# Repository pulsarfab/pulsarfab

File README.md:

# PulsarFab

Open-source astronomy hardware platform — dew heater controllers, power distribution and USB hubs, mount accessories, and other observatory gear based on STM32 and ESP32-S3 microcontrollers.

## Projects

| Project | Description | MCU | Flash/RAM | Framework | Status |
|---------|-------------|-----|-----------|-----------|--------|
| **pulsardew** | USB dew heater controller | STM32G0B1KBU6 | 128KB/144KB | STM32 HAL + FreeRTOS | 🚧 In Development |
| **[PulsarPower](hardware/pulsardewhub/README.md)** | Power distribution, two dew heaters and four-port USB 2.0 hub | STM32G0B1KBU6 | 128KB/144KB | Firmware adaptation pending | 🚧 Connected schematic / unrouted floorplan |
| **pulsardewpro** | WiFi dew heater controller (ASCOM Alpaca) | ESP32-S3-MINI-1 | 8MB/512KB | ESP-IDF | 🚧 In Development |
| **crunchdefender** | Skywatcher mount limit guard — inline USB host/device that interrupts motion before the OTA collides with the pier or cables crunch | STM32F405RGT6 | 1024KB/192KB | STM32 HAL | 🌱 Bootstrapped |

## Repository Structure

```
pulsarfab/
├── firmware/                 # All firmware projects (C/C++, Apache 2.0)
│   ├── pulsardew/             # STM32G0B1 USB dew heater controller
│   ├── pulsardewpro/          # ESP32-S3 WiFi dew heater (ASCOM Alpaca)
│   ├── crunchdefender/        # STM32F405 mount limit guard (dual-USB)
│   ├── common/                # Shared STM32 HAL and utilities
│   └── shared/                # Shared protocol definitions and libraries
├── hardware/                 # PCB designs (CERN-OHL-S v2 + NC)
│   ├── pulsardew/            # USB dew heater PCB
│   ├── pulsardewhub/         # PulsarPower power / dew / USB hub PCB
│   ├── pulsardewpro/         # WiFi dew heater PCB
│   ├── crunchdefender/       # Mount limit guard PCB
│   └── lib/                  # Shared KiCad libraries
├── mechanical/               # 3D models (coming soon, CERN-OHL-S v2 + NC)
└── LICENSE                   # Dual licensing information
```

## Quick Start

### Prerequisites

**For STM32 builds (pulsardew):**
- ARM GCC toolchain: `arm-none-eabi-gcc`
- CMake 3.20 or newer
- Make or Ninja build tool

**For ESP32-S3 builds (pulsardewpro):**
- ESP-IDF v5.x
- Python 3.10+
- uv (Python package manager)

See [firmware/README.md](firmware/README.md) for detailed installation instructions.

### Build Projects

```bash
# STM32 USB dew heater
cd firmware
make pulsardew-g0b1              # Build pulsardew (STM32G0B1)
make flash-pulsardew-g0b1        # Flash via st-flash

# STM32 mount limit guard
cd firmware
make crunchdefender-f405         # Build crunchdefender (STM32F405)
make flash-crunchdefender-f405   # Flash via st-flash

# ESP32-S3 WiFi dew heater
cd firmware/pulsardewpro
idf.py build                     # Build with ESP-IDF
idf.py flash                     # Flash via USB
```

## Key Features

### Dew Heater Control
- PWM-controlled heater outputs for telescope optics
- Temperature and humidity sensing (SHT40)
- Ambient dew point calculation with automatic heater regulation
- Configurable temperature setpoints per channel

### PulsarDew (USB)
- 4 PWM heater channels with current sensing
- Temperature/humidity sensor (SHT40 via I2C)
- USB 2.0 FS device (CDC for serial control from PC)
- Dew point calculation and automatic regulation
- Compact STM32G0B1 design with FreeRTOS

### PulsarDewPro (WiFi / ASCOM Alpaca)
- 4 PWM heater channels with individual current sensing
- Multiple temperature/humidity sensors
- WiFi 802.11 b/g/n connectivity
- ASCOM Alpaca REST API (ObservingConditions + Switch devices)
- Web configuration UI
- OTA firmware updates
- ESP32-S3 with ESP-IDF

### PulsarPower (Power / Dew / USB)
- Four independently switched, current-monitored DC outlets, **5 A service target each**
- Positive-side DC switching with grounded returns; static on/off, no PWM on DC outlets
- Two PWM dew heater channels
- Four external USB 2.0 ports, **500 mA per port**, plus an internal connection to the controller
- **12–18 V nominal input**, with alternative XT60 or barrel assembly options
- **25 A shared XT60 continuous target**; barrel option has a **3.5 A provisional continuous budget**
- **5 V / 3 A regulator** shared by USB and onboard electronics; not 3 A per USB port

PulsarDew remains the original dedicated dew controller. **PulsarPower** is the
expanded product, previously called **PulsarDew Hub** during development. Its
KiCad files and Makefile targets currently retain the `pulsardewhub` identifier.
The 0.3 draft has a connected schematic and an unrouted four-layer floorplan;
current ratings require routing and prototype qualification, and firmware
adaptation is pending. Cost reductions retain outlet current monitoring: TPS25974L
switches, one shared voltage window and two owned SiR680LDP input FETs. See the [PulsarPower design README](hardware/pulsardewhub/README.md)
for the power budget, schematic, floorplan and remaining release work.

PulsarPower and PulsarDew now share stocked XKB barrel sockets and HRO USB-C sockets;
SHT40 R2 is retained. The shared procurement CSV allocates 110 owned XKB sockets.
U30 now uses 22 allocated owned LMR51610s for the 20-board batch plus spares.
See the [LMR51610 implementation notes](hardware/pulsardewhub/docs/lmr51610-commonality.md)
for the 3.3 V / 650 mA logic stage; the 5 V / 3 A USB supply remains.

## Hardware

### PulsarDew (STM32G0B1KBU6)
- 128KB Flash, 144KB RAM
- ARM Cortex-M0+ @ 64MHz
- UFQFPN-32 package
- USB 2.0 FS (HSI48 + CRS, no external crystal)
- FreeRTOS real-time control

### PulsarDewPro (ESP32-S3-MINI-1)
- 8MB Flash, 512KB SRAM
- Dual-core Xtensa LX7 @ 240MHz
- WiFi 802.11 b/g/n
- USB-OTG for programming
- ASCOM Alpaca server

### CrunchDefender (STM32F405RGT6)
- 1024KB Flash, 192KB RAM (128KB SRAM + 64KB CCM)
- ARM Cortex-M4F @ 168MHz with single-precision FPU
- LQFP-64 package
- **Two USB peripherals running concurrently** — OTG_FS as device (PA11/PA12) to the host PC, OTG_HS-in-FS-mode as host (PB14/PB15) to the Skywatcher hand controller
- Sits inline on the USB link, parses position telemetry, intercepts motion commands when limits are exceeded

## License

This project uses dual licensing:

- **Firmware/Software**: [Apache 2.0](firmware/LICENSE)
- **Hardware Designs**: CERN-OHL-S v2 (strongly reciprocal) + Non-Commercial restriction

See [LICENSE](LICENSE) for details.

## Contributing

Contributions are welcome! Please ensure:
- Firmware contributions follow the Apache 2.0 license
- Hardware contributions follow CERN-OHL-S v2 + NC
- Code follows the existing style
- All changes are tested

## Resources

### Hardware
- [STM32G0 Series](https://www.st.com/en/microcontrollers-microprocessors/stm32g0-series.html)
- [ESP-IDF Documentation](https://docs.espressif.com/projects/esp-idf/)
- [ASCOM Alpaca](https://ascom-standards.org/Developer/Alpaca.htm)

### Licenses
- [Apache 2.0 License](https://www.apache.org/licenses/LICENSE-2.0)
- [CERN-OHL-S v2](https://ohwr.org/cern_ohl_s_v2.txt)

### Tools
- [uv Python Package Manager](https://github.com/astral-sh/uv)

---

Copyright (c) 2025-2026 Yann Ramin

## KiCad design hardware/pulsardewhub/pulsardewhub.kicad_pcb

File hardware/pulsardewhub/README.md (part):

# PulsarPower — power distribution, dew control and USB hub

**PulsarPower** is the expanded power product derived from the original
**[PulsarDew](../pulsardew/README.md)** dew heater controller. It combines four
switched DC outlets, two dew heaters and a four-port USB 2.0 hub. Earlier design
documents call it **PulsarDew Hub**; the directory, KiCad filenames and Makefile
targets currently retain `pulsardewhub` as their internal project identifier.

Revision **0.3-draft**, reviewed with KiCad 10.0.6 on 2026-10-03. Open
`pulsardewhub.kicad_pro` in KiCad. This is a separate design derived from
PulsarDew, with **two PWM heaters, four individually switched and current-monitored
DC outlets, and four external USB 2.0 ports**. DC outlets use static on/off GPIO;
they must not be PWM controlled.

The schematic is electrically connected and the native PCB is a placed,
**unrouted 180 × 110 mm four-layer floorplan**. It is not ready for fabrication.
There are no tracks, vias or copper fills. No enclosure is assumed.

Review the [15-page schematic PDF](docs/schematic.pdf) and
[annotated footprint placement](docs/pcb-placement.png) without opening KiCad.

## Ratings and assembly options

| Item | Design target / constraint |
| --- | --- |
| Input | **12–18 V DC (18 V maximum including supply tolerance)**, as selected for this revision |
| XT60 configuration | Fit J10 + F10; **25 A shared continuous target**, pending thermal/copper validation |
| Barrel configuration | Fit J11 + F11 instead; **5 A absolute total ceiling**, **3.5 A provisional continuous budget** after fuse derating |
| DC outlets | Four center-positive **2.0 mm** barrel sockets, 5 A service target each; independent high-side switch, analog current monitor and power-good signal |
| Heater outputs | Two screw terminals, 5 A target each; fused positive pin 1 and PWM switched return pin 2 |
| USB | Four USB-A downstream ports, 500 mA service per port; USB-C upstream data connection |

The **5 V regulator is rated for 3 A total**. Four USB ports reserve 2 A at
500 mA each; a provisional 0.6 A equivalent budget for onboard logic/support
leaves about 0.4 A margin. This is a design budget pending thermal and transient
testing, not an additional external 5 V output rating.

**Populate one input path only. Do not fit/connect both inputs.** J11 and F11
are DNP in the default XT60 assembly. There is no isolation between the two
input connector paths. The barrel option cannot support four loaded 5 A outlets.
At 20 A of DC outlet load, the XT60 target leaves about 5 A of input current for
the heaters, USB conversion and logic together. Six simultaneous 5 A loads are
outside this design budget. The external supply must be current limited and
the wiring/fuses must be coordinated with the final assembly.

F10 is a 30 A S1032 fuse; F11 is a 5 A Littelfuse 451. Heater fuses are 7 A
Littelfuse 451 devices to allow a 5 A service target after room-temperature
derating. Fuse markings are not continuous board-current ratings; ambient
temperature, enclosure, cable ratings and time/current curves still govern.

## Connected hierarchy

There are 15 schematic pages in nine source files. Root-sheet wires connect
the system rails, I2C, heater control, four DC interfaces and USB data/control.
Repeated sheets have distinct references and net identities.

| Sheet | Circuit |
| --- | --- |
| Power input | Alternative fused inputs, LM74700 + two parallel SiR680LDP reverse-polarity/reverse-current stage, SMCJ18A TVS, 470 µF bulk |
| DC supplies | LMR33630 input-to-5.02 V / 3 A; owned LMR51610 5 V-to-3.3 V logic stage, 650 mA budget |
| Controller | STM32G0B1KBU6, SWD/reset, SHT40, I2C pull-ups, ADC filters and GPIO connections |
| Heaters | TC4427A active-high gate driver, two AOD4184A switches, individual fuses/clamps, combined-current INA226 and 2 mΩ shunt |
| DC protection | One TPS3700 UV/OV window plus SN74LVC08 quad AND gate; four independent default-off commands |
| DC outlet ×4 | TPS25974LRPWR circuit breaker, local OVLO, ILM/current filter, latch-off, PG divider/pull-up, TVS1800 input clamp and SS54 output clamp |
| USB hub | USB2517, 24 MHz crystal, reset supervisor, configuration straps, protected USB-C upstream connection |
| USB port ×4 | TPS2553 current-limited VBUS switch, USBLC6 ESD, USB-A socket, 150 µF bulk and ceramic bypass |

The seven-port USB2517 uses port 1 for the onboard STM32 and ports 2–5 for the
four external sockets. Ports 6 and 7 are disabled by straps. The hub is
self-powered, with individual downstream power control. Its two internal 1.8 V
regulator outputs each have their own capacitor and are not tied together.
Host VBUS is used only for detection and upstream ESD protection, with no
connection to the board's 5 V supply. The selected 150 µF ±20% downstream
capacitors retain at least 120 µF at nominal tolerance.

The LM74700 input circuit is not an overvoltage disconnect. Do not apply more
than 18 V nominal; the TVS is for transients, not sustained excess input voltage.
DC output switches have no external reverse-blocking FET, so **do not backfeed
the DC outlets**. Heater return pins must not be connected directly to ground.

## MCU interface and firmware changes

| Function | STM32 signal / physical pad |
| --- | --- |
| Heater 0 / 1 | PA0 / PA1, pads 7 / 8, active-high PWM |
| DC enable 1 / 2 / 3 / 4 | PB0 / PB1 / PB2 / PB9, pads 15 / 16 / 17 / 1; static GPIO only |
| DC current ADC 1–4 | PA4–PA7, pads 11–14 |
| DC power-good 1 / 2 / 3 / 4 | PB3 / PB4 / PB5 / PC6, pads 27 / 28 / 29 / 20; high = output ready |
| USB D− / D+ | PA11 / PA12, pads 22 / 23, internal hub port 1 |
| USB attach permission | PA9, pad 19, hub port 1 PWR output |
| I2C SCL / SDA | PB6 / PB7, pads 30 / 31; INA226 0x40, SHT40 0x44 |
| SWDIO / SWCLK / NRST | PA13 / PA14 / PF2, pads 24 / 25 / 6 |

The original firmware is not a drop-in image: heater polarity and channel count,
ADC inputs, outlet GPIO and hub attachment behavior have changed. Disable the
MCU UCPD dead-battery function on PA9, and detach USB whenever USB_ATTACH is low.
Initialize heater and DC enables low. Overcurrent/thermal faults latch off until
reset through the enable signal; do not repeatedly retry a short circuit.
`DC_PG1..4` replaces the former `DC_FLT1..4` labels on the same MCU pins. PG low
also means disabled, starting, or voltage-inhibited. Qualify PG against the
commanded state and allow startup settling. The voltage window is an automatic
hardware inhibit: recovery can re-enable a still-asserted GPIO and can reset a
latched fault by pulling EN low. Firmware should deassert ENABLE after an
unexpected PG loss if an explicit user restart is required.

Heater inputs and gates have pull-downs, and the new non-inverting driver
addresses the original driver's dependence on a live 3.3 V rail for default-off
behavior. Validate startup, brownout and loss of each rail on hardware; this is
not a certified safety shutdown. The INA226 measures **combined heater current**;
the four DC currents are measured independently through TPS25974 ILM outputs.

With a **1 kΩ ILM resistor**, the nominal ADC slope is **0.1055 V/A**
(**0.5275 V at 5 A**). ILM sets the breaker threshold and provides the current
signal. The 10 kΩ / 10 nF filter isolates ADC capacitance from this pin; do not
put a capacitor directly on ILM. Gain limits are 98–114 µA/A for currents from
1 A to the configured limit. Include source impedance in ADC acquisition-time
settings and calibrate each channel. Readings during a short are not guaranteed.

The nominal breaker setting is **5747 / 1000 = 5.747 A**, allowing a **5 A
service target**. A ±10% threshold screening plus 1% resistor tolerance and an
additional 1% TCR allowance gives approximately **5.07–6.45 A**; this calculation
is not a substitute for measured trip/no-trip limits. ITIMER is open for the
fastest response. The **L** variant latches after overcurrent/thermal faults;
cycle enable to recover. The separate fast-trip threshold is nominally 2.01×
ILIM (1.70–2.40× specified ratio). The 4.7 nF slew capacitor targets 0.702 V/ms,
or about 25.6 ms at 18 V. Verify startup with actual capacitive loads.

One **TPS3700** provides the common hardware voltage window: **9.2 V rising
UV** and **19.2 V rising OV**, using 220 kΩ/10 kΩ and 470 kΩ/10 kΩ dividers.
Its open-drain outputs are tied together and pulled up through 10 kΩ. A
**SN74LVC08** computes `outlet_enable[i] = command[i] AND window_ok` independently
for each port. Each command has a 10 kΩ pull-down. Each eFuse has a 10 kΩ enable
pull-down and 1 kΩ series input resistor. The shared window is a common failure
point, not a redundant safety circuit. Reset, brownout and loss-of-rail tests
remain required.

Each eFuse retains its own fast OVLO divider (150 kΩ / 10 kΩ, 19.2 V nominal;
about 18.57–20.04 V including thresholds, resistor tolerances and leakage).
PGTH uses 100 kΩ / 20 kΩ for about 7.2 V rising. PG high also requires completion
of startup; it is an output-ready indication, not a precision output voltmeter.
Neither inhibit disconnects VIN from the ICs, bucks or heaters. Recovery can
re-enable an asserted GPIO, so firmware must deassert the command after an
unexpected PG loss when manual restart is required.

The new eFuse supports −40°C to +125°C junction temperature; **−15°C remains the
accepted lower product target**. Its input absolute maximum is 28 V. Each old
SMBJ18A local clamp was replaced by **TVS1800DRVR**, whose 24.7 V maximum clamp
applies to the datasheet's specified 35 A, 8/20 µs, 125°C pulse condition. This
leaves voltage margin, but does not establish a system surge rating: final
loops, source impedance, pulse energy and overshoot must be tested. The TVS1800
has an 18 V standoff rating; supply tolerance must stay within that limit.

**Q10 and Q11 are parallel SiR680LDP input MOSFETs from shared stock.** They are
80 V parts with ±20 V gates and 2.5 V maximum threshold. At 25 A total, equal
sharing and 3.55 mΩ maximum RDS(on) at 4.5 V gate drive/25°C give **1.11 W total**
conduction loss. Applying an illustrative 1.6× hot-resistance factor gives
1.78 W total; current sharing and temperature remain layout/bench checks.
Use symmetric short source/drain paths, common low-inductance gate routing,
and thermal copper. The Vishay PowerPAK SO-8 footprint uses pad 5 for the
exposed drain and physical drain leads 5–8; source is 1–3 and gate is 4.
C10 is now 1 µF/50 V, exceeding LM74700's `10 × combined Ciss` recommendation
(145 nF for two 7.25 nF devices) with substantial capacitance margin. C13 adds
local raw-input bypass. Gate charge is 90 nC typical/135 nC maximum **per FET at
10 V**, and startup/body-diode stress must be checked with the selected supply.

## PCB floorplan and routing intent

The floorplan contains 226 schematic footprints, four M3 holes and three
fiducials. Mount centers are 4 mm from the edges (172 × 102 mm spacing).
USB connectors occupy the top edge; their switches, ESD devices and bulk caps
are nearby. The hub is behind the downstream ports with the MCU to its left.
DC switches and their output connectors occupy four regions along the bottom.
The two heater stages occupy the lower-left region. Input protection and bucks
sit at the left. SHT40 is at the right edge, with a copper keepout beneath the
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
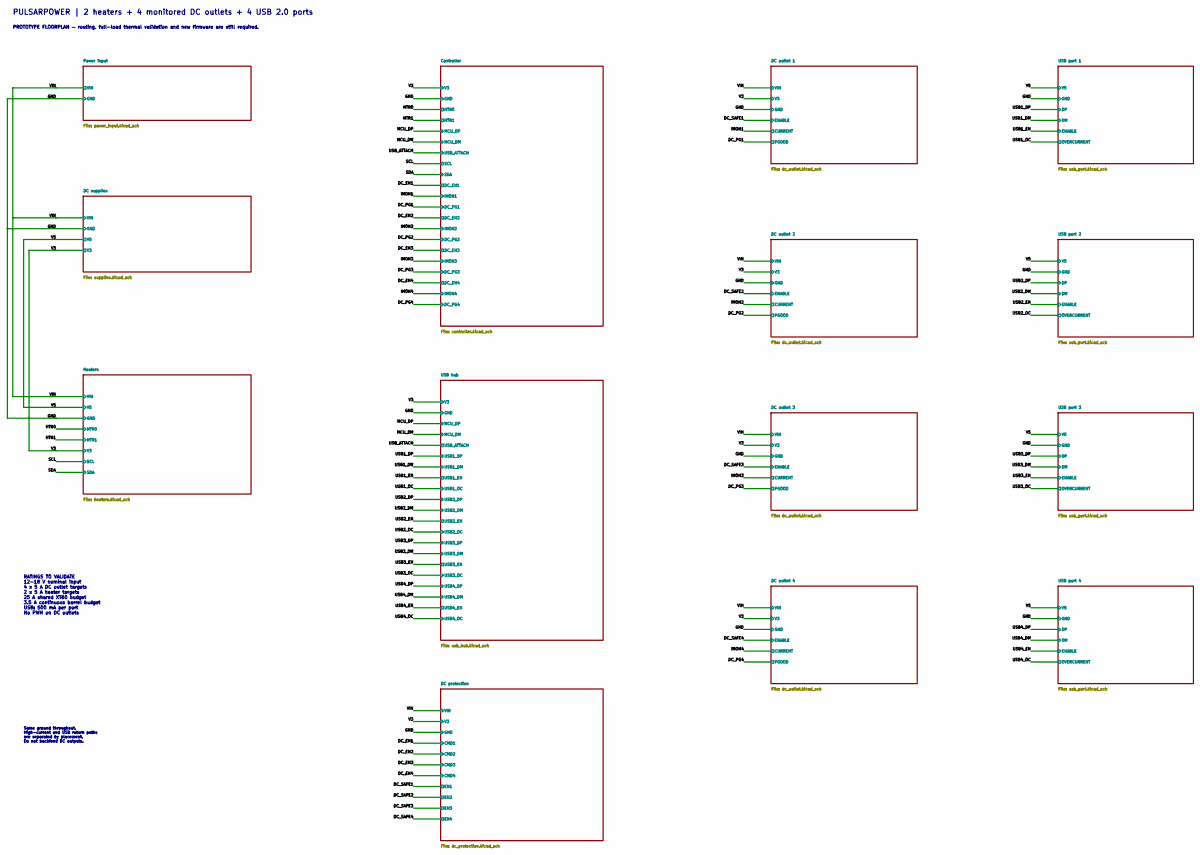
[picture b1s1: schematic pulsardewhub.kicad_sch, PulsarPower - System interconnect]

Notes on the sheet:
PULSARPOWER | 2 heaters + 4 monitored DC outlets + 4 USB 2.0 ports
PROTOTYPE FLOORPLAN — routing, full-load thermal validation and new firmware are still required.
RATINGS TO VALIDATE 12-18 V nominal input 4 x 5 A DC outlet targets 2 x 5 A heater targets 25 A shared XT60 budget 3.5 A continuous barrel budget USB: 500 mA per port No PWM on DC outlets
Same ground throughout. High-current and USB return paths are separated by placement. Do not backfeed DC outputs.

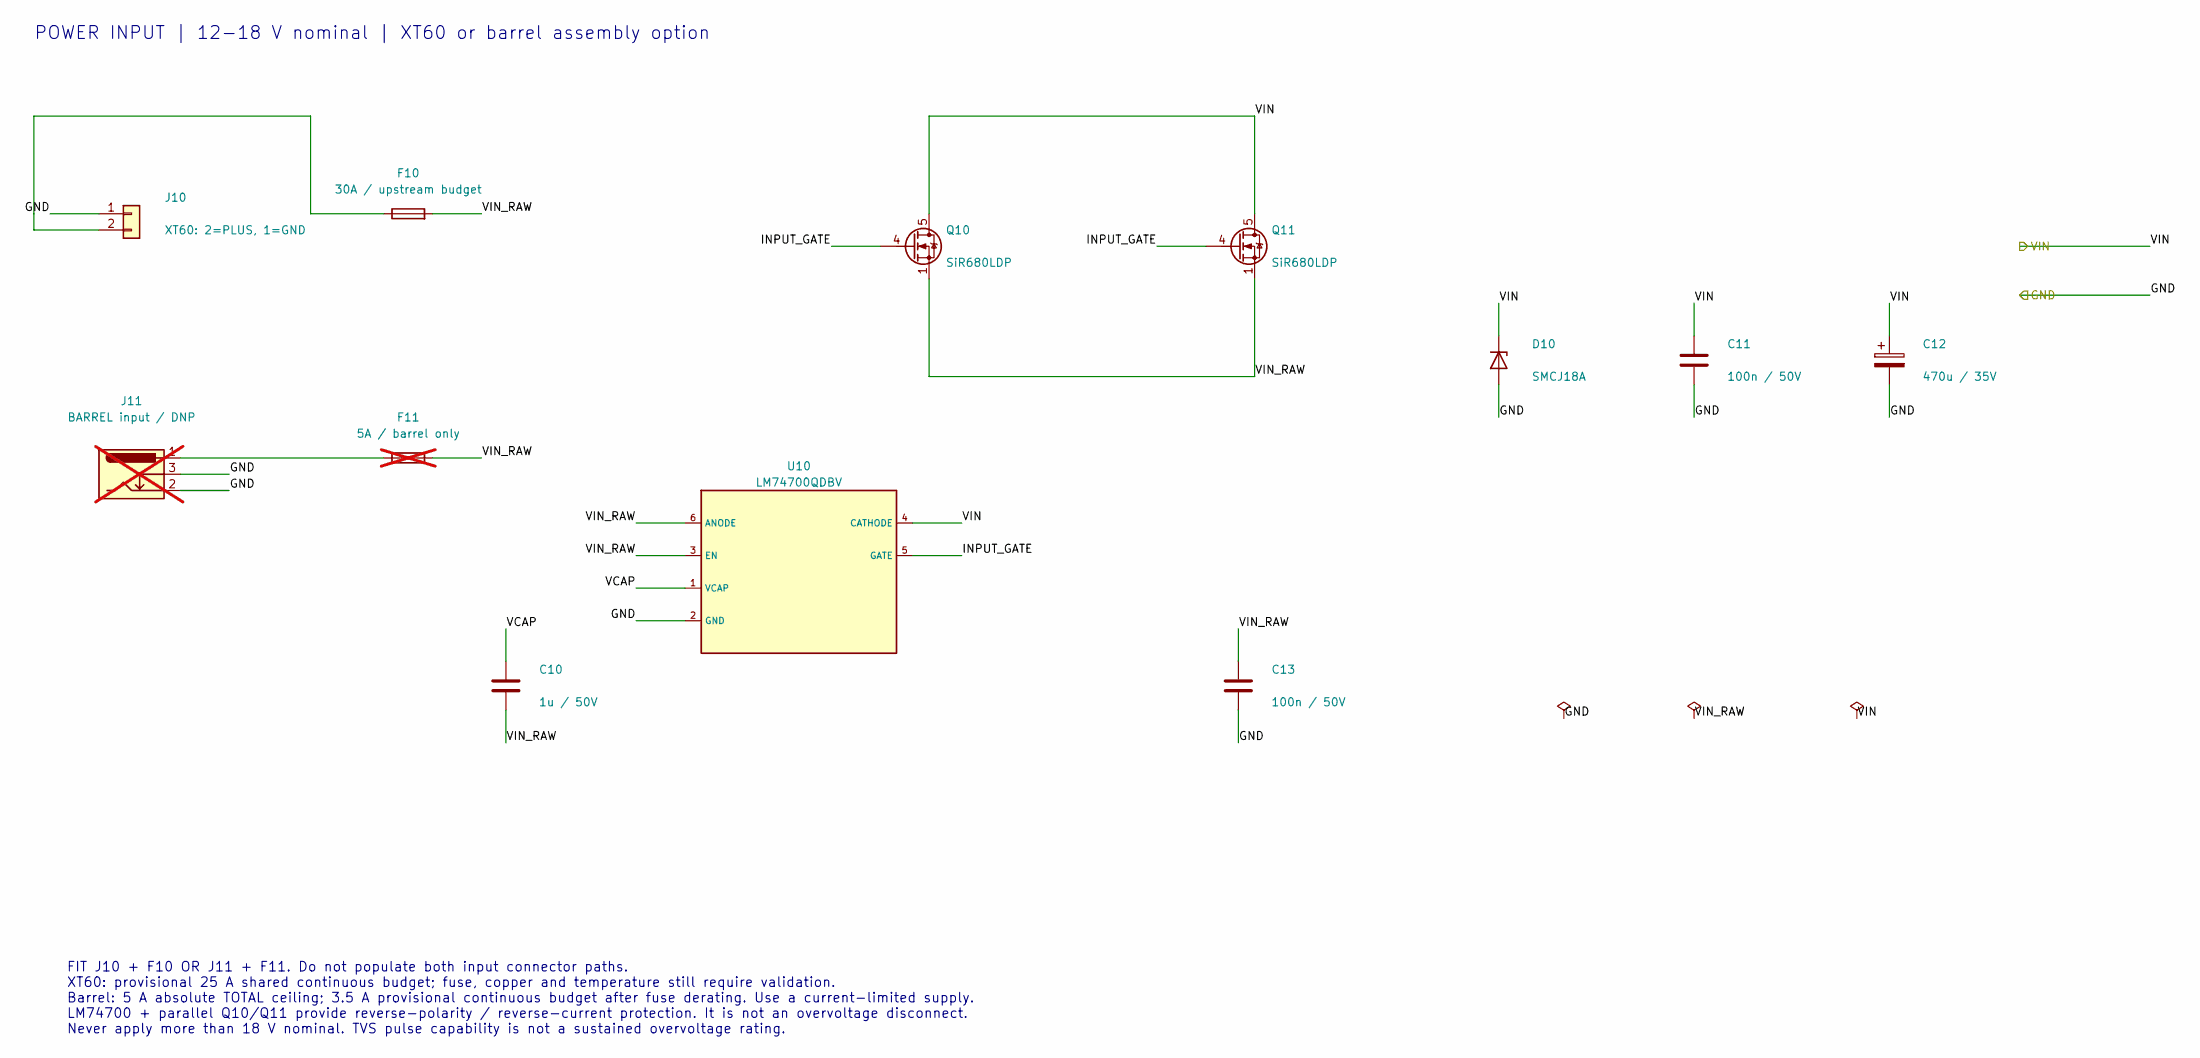
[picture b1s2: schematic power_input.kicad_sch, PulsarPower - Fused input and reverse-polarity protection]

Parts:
C10: 1u / 50V; C_0603_1608Metric; MPN CL10A105KB8NNNC; LCSC C15849
C11, C13: 100n / 50V; C_0603_1608Metric; MPN CC0603KRX7R9BB104; LCSC C14663
C12: 470u / 35V; CP_Radial_D10.0mm_P5.00mm; MPN ERS1VM471G16OT; LCSC C106703
D10: SMCJ18A; D_SMC; MPN SMCJ18A; LCSC C438102
F10: 30A / upstream budget; Fuse_S1032_10.3x3.2mm; MPN S1032-F-30.0A; LCSC C553917
F11: 5A / barrel only; Fuse_Littelfuse-NANO2-451_453; MPN 0451005.MRL; LCSC C48467; not fitted
J10: XT60: 2=PLUS, 1=GND; AMASS_XT60PW-M_Edge; MPN XT60PW-M; LCSC C98732
J11: BARREL input / DNP; BarrelJack_XKB_DC-005K-5A_Edge; MPN DC-005K-5A-2.0; LCSC C2880546; not fitted
Q10, Q11: SiR680LDP; PowerPAK_SO-8_Single; MPN SIR680LDP-T1-RE3; LCSC C3279524
U10: LM74700QDBV; SOT-23-6; MPN LM74700QDBVRQ1; LCSC C2941042

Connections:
/GND: C11.2, C12.2, C13.2, D10.2 (A), J10.1, J11.2, J11.3, U10.2 (GND); also elsewhere on the board
/Power input/INPUT_GATE: Q10.4 (G), Q11.4 (G), U10.5 (GATE)
/Power input/VCAP: C10.1, U10.1 (VCAP)
/Power input/VIN_RAW: C10.2, C13.1, F10.2, F11.2, Q10.1 (S), Q10.2 (S), Q10.3 (S), Q11.1 (S), Q11.2 (S), Q11.3 (S), U10.3 (EN), U10.6 (ANODE)
/VIN: C11.1, C12.1, D10.1 (K), Q10.5 (D), Q11.5 (D), U10.4 (CATHODE); also elsewhere on the board
unnamed: F11.1, J11.1
unnamed: F10.1, J10.2

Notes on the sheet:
POWER INPUT | 12-18 V nominal | XT60 or barrel assembly option
FIT J10 + F10 OR J11 + F11. Do not populate both input connector paths. XT60: provisional 25 A shared continuous budget; fuse, copper and temperature still require validation. Barrel: 5 A absolute TOTAL ceiling; 3.5 A provisional continuous budget after fuse derating. Use a current-limited supply. 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

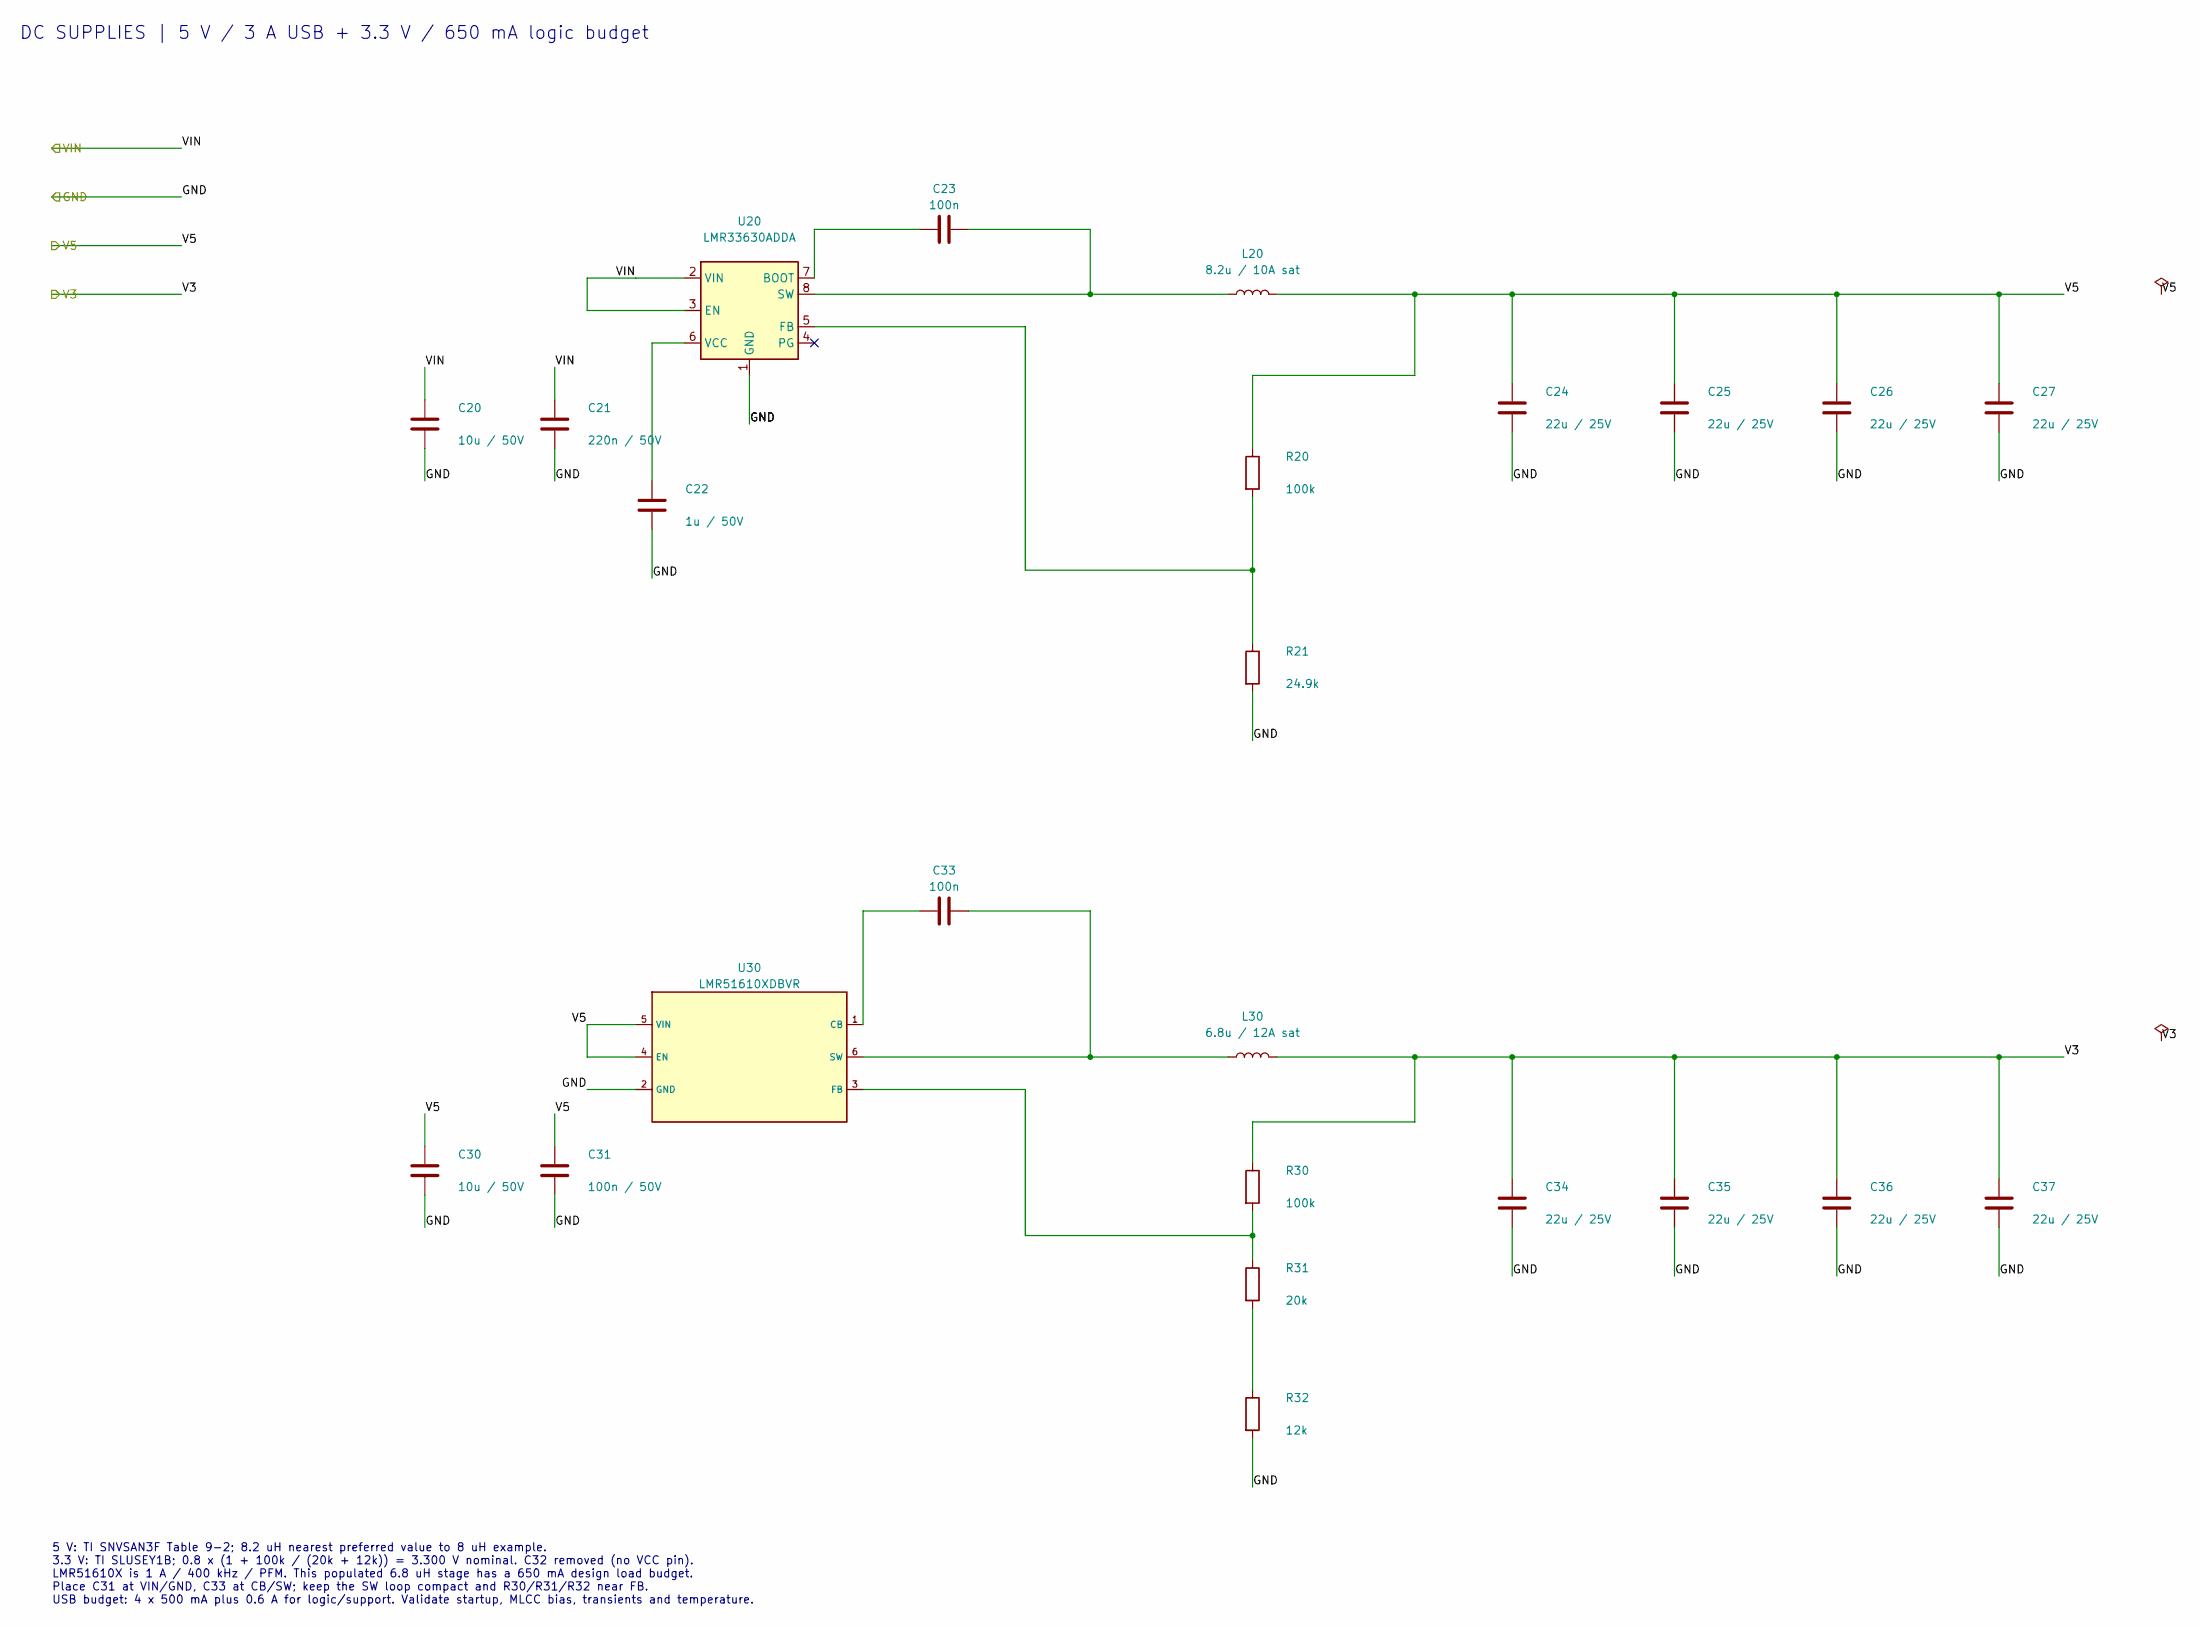
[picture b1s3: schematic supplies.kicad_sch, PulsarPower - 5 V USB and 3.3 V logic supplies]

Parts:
C20, C30: 10u / 50V; C_1210_3225Metric; MPN CL32B106KBJNNNE; LCSC C138687
C21: 220n / 50V; C_0603_1608Metric; MPN CL10B224KB8NNNC; LCSC C64705
C22: 1u / 50V; C_0603_1608Metric; MPN CL10A105KB8NNNC; LCSC C15849
C23, C33: 100n; C_0603_1608Metric; MPN CC0603KRX7R9BB104; LCSC C14663
C24, C25, C26, C27, C34, C35, C36, C37: 22u / 25V; C_1206_3216Metric; MPN CL31A226KAHNNNE; LCSC C12891
C31: 100n / 50V; C_0603_1608Metric; MPN CC0603KRX7R9BB104; LCSC C14663
L20: 8.2u / 10A sat; L_SXN_SMMS1050; MPN SMMS1050-8R2M; LCSC C149543
L30: 6.8u / 12A sat; L_SXN_SMMS1050; MPN SMMS1050-6R8M; LCSC C149542
R20, R30: 100k; R_0603_1608Metric; MPN 0603WAF1003T5E; LCSC C25803
R21: 24.9k; R_0603_1608Metric; MPN 0603WAF2492T5E; LCSC C25962
R31: 20k; R_0603_1608Metric; MPN 0603WAF2002T5E; LCSC C4184
R32: 12k; R_0603_1608Metric; MPN 0603WAF1202T5E; LCSC C22790
U20: LMR33630ADDA; Texas_HSOP-8-1EP_3.9x4.9mm_P1.27mm; MPN LMR33630ADDAR; LCSC C841384
U30: LMR51610XDBVR; SOT-23-6; MPN LMR51610XDBVR; LCSC C20539658

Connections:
/GND: C20.2, C21.2, C22.2, C24.2, C25.2, C26.2, C27.2, C30.2, C31.2, C34.2, C35.2, C36.2, C37.2, R21.2, R32.2, U20.1 (GND), U20.9 (GND), U30.2 (GND); also elsewhere on the board
/V3: C34.1, C35.1, C36.1, C37.1, L30.2, R30.1; also elsewhere on the board
/V5: C24.1, C25.1, C26.1, C27.1, C30.1, C31.1, L20.2, R20.1, U30.4 (EN), U30.5 (VIN); also elsewhere on the board
/VIN: C20.1, C21.1, U20.2 (VIN), U20.3 (EN); also elsewhere on the board
unnamed: R31.2, R32.1
unnamed: C23.1, U20.7 (BOOT)
unnamed: R20.2, R21.1, U20.5 (FB)
unnamed: C23.2, L20.1, U20.8 (SW)
unnamed: C22.1, U20.6 (VCC)
unnamed: C33.1, U30.1 (CB)
unnamed: R30.2, R31.1, U30.3 (FB)
unnamed: C33.2, L30.1, U30.6 (SW)

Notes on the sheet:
DC SUPPLIES | 5 V / 3 A USB + 3.3 V / 650 mA logic budget
5 V: TI SNVSAN3F Table 9-2; 8.2 uH nearest preferred value to 8 uH example. 3.3 V: TI SLUSEY1B; 0.8 x (1 + 100k / (20k + 12k)) = 3.300 V nominal. C32 removed (no VCC pin). LMR51610X is 1 A / 400 kHz / PFM. This populated 6.8 uH stage has a 650 mA design load budget. Place C31 at VIN/GND, C33 at CB/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

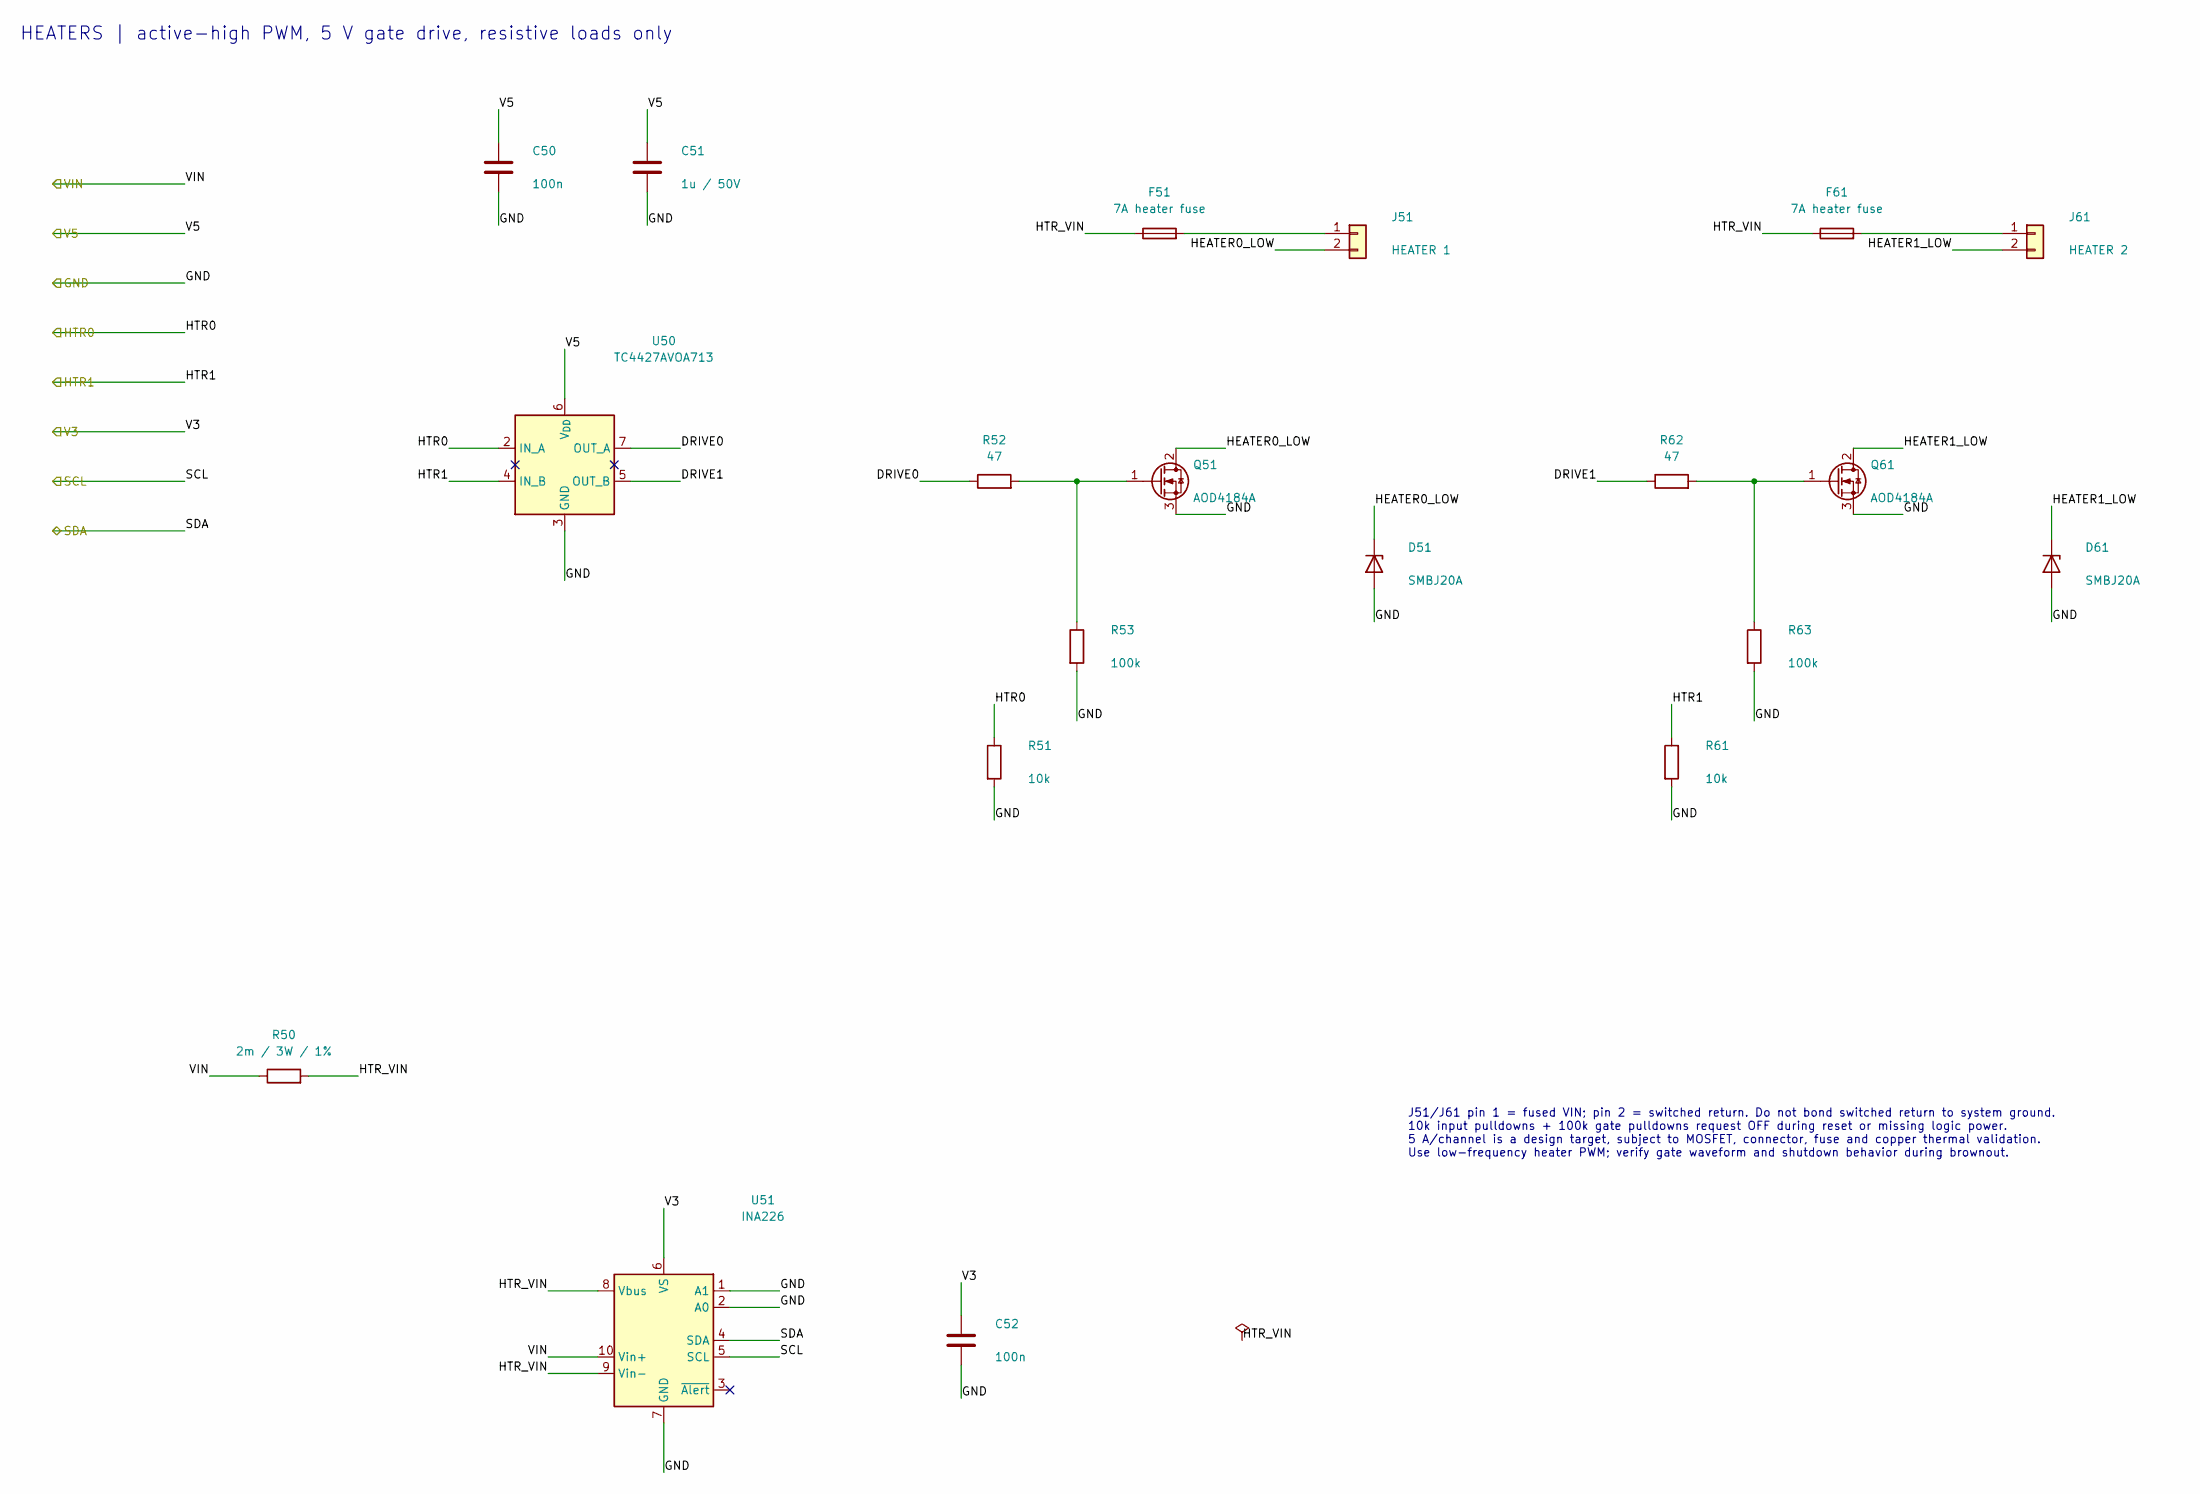
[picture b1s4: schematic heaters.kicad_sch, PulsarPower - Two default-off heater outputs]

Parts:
C50, C52: 100n; C_0603_1608Metric; MPN CC0603KRX7R9BB104; LCSC C14663
C51: 1u / 50V; C_0603_1608Metric; MPN CL10A105KB8NNNC; LCSC C15849
D51, D61: SMBJ20A; D_SMB; MPN SMBJ20A; LCSC C364296
F51, F61: 7A heater fuse; Fuse_Littelfuse-NANO2-451_453; MPN 0451007.MRL; LCSC C99548
J51: HEATER 1; TerminalBlock_KEFA_KF128_2P_P5.08mm; MPN KF128-5.08-2P-AA; LCSC C474952
J61: HEATER 2; TerminalBlock_KEFA_KF128_2P_P5.08mm; MPN KF128-5.08-2P-AA; LCSC C474952
Q51, Q61: AOD4184A; TO-252-2; MPN AOD4184A; LCSC C5370959
R50: 2m / 3W / 1%; R_2512_6332Metric; MPN HoLLR2512-3W-2mR-1%; LCSC C2994640
R51, R61: 10k; R_0603_1608Metric; MPN 0603WAF1002T5E; LCSC C25804
R52, R62: 47; R_0603_1608Metric; MPN 0603WAF470JT5E; LCSC C23182
R53, R63: 100k; R_0603_1608Metric; MPN 0603WAF1003T5E; LCSC C25803
U50: TC4427AVOA713; SOIC-8_3.9x4.9mm_P1.27mm; MPN TC4427AVOA713; LCSC C624944
U51: INA226; TSSOP-10_3x3mm_P0.5mm; MPN INA226AIDGSR; LCSC C49851

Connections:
/GND: C50.2, C51.2, C52.2, D51.2 (A), D61.2 (A), Q51.3 (S), Q61.3 (S), R51.2, R53.2, R61.2, R63.2, U50.3 (GND), U51.1 (A1), U51.2 (A0), U51.7 (GND); also elsewhere on the board
/HTR0: R51.1, U50.2 (IN_A); also elsewhere on the board
/HTR1: R61.1, U50.4 (IN_B); also elsewhere on the board
/Heaters/DRIVE0: R52.1, U50.7 (OUT_A)
/Heaters/DRIVE1: R62.1, U50.5 (OUT_B)
/Heaters/HEATER0_LOW: D51.1 (K), J51.2, Q51.2 (D)
/Heaters/HEATER1_LOW: D61.1 (K), J61.2, Q61.2 (D)
/Heaters/HTR_VIN: F51.1, F61.1, R50.2, U51.8 (Vbus), U51.9 (Vin-)
/SCL: U51.5 (SCL); also elsewhere on the board
/SDA: U51.4 (SDA); also elsewhere on the board
/V3: C52.1, U51.6 (VS); also elsewhere on the board
/V5: C50.1, C51.1, U50.6 (V_{DD}); also elsewhere on the board
/VIN: R50.1, U51.10 (Vin+); also elsewhere on the board
unnamed: F51.2, J51.1
unnamed: F61.2, J61.1
unnamed: Q51.1 (G), R52.2, R53.1
unnamed: Q61.1 (G), R62.2, R63.1

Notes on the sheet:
HEATERS | active-high PWM, 5 V gate drive, resistive loads only
J51/J61 pin 1 = fused VIN; pin 2 = switched return. Do not bond switched return to system ground. 10k input pulldowns + 100k gate pulldowns request OFF during reset or missing logic power. 5 A/channel is a design target, subject to MOSFET, connector, fuse and copper thermal validation. Use low-freq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

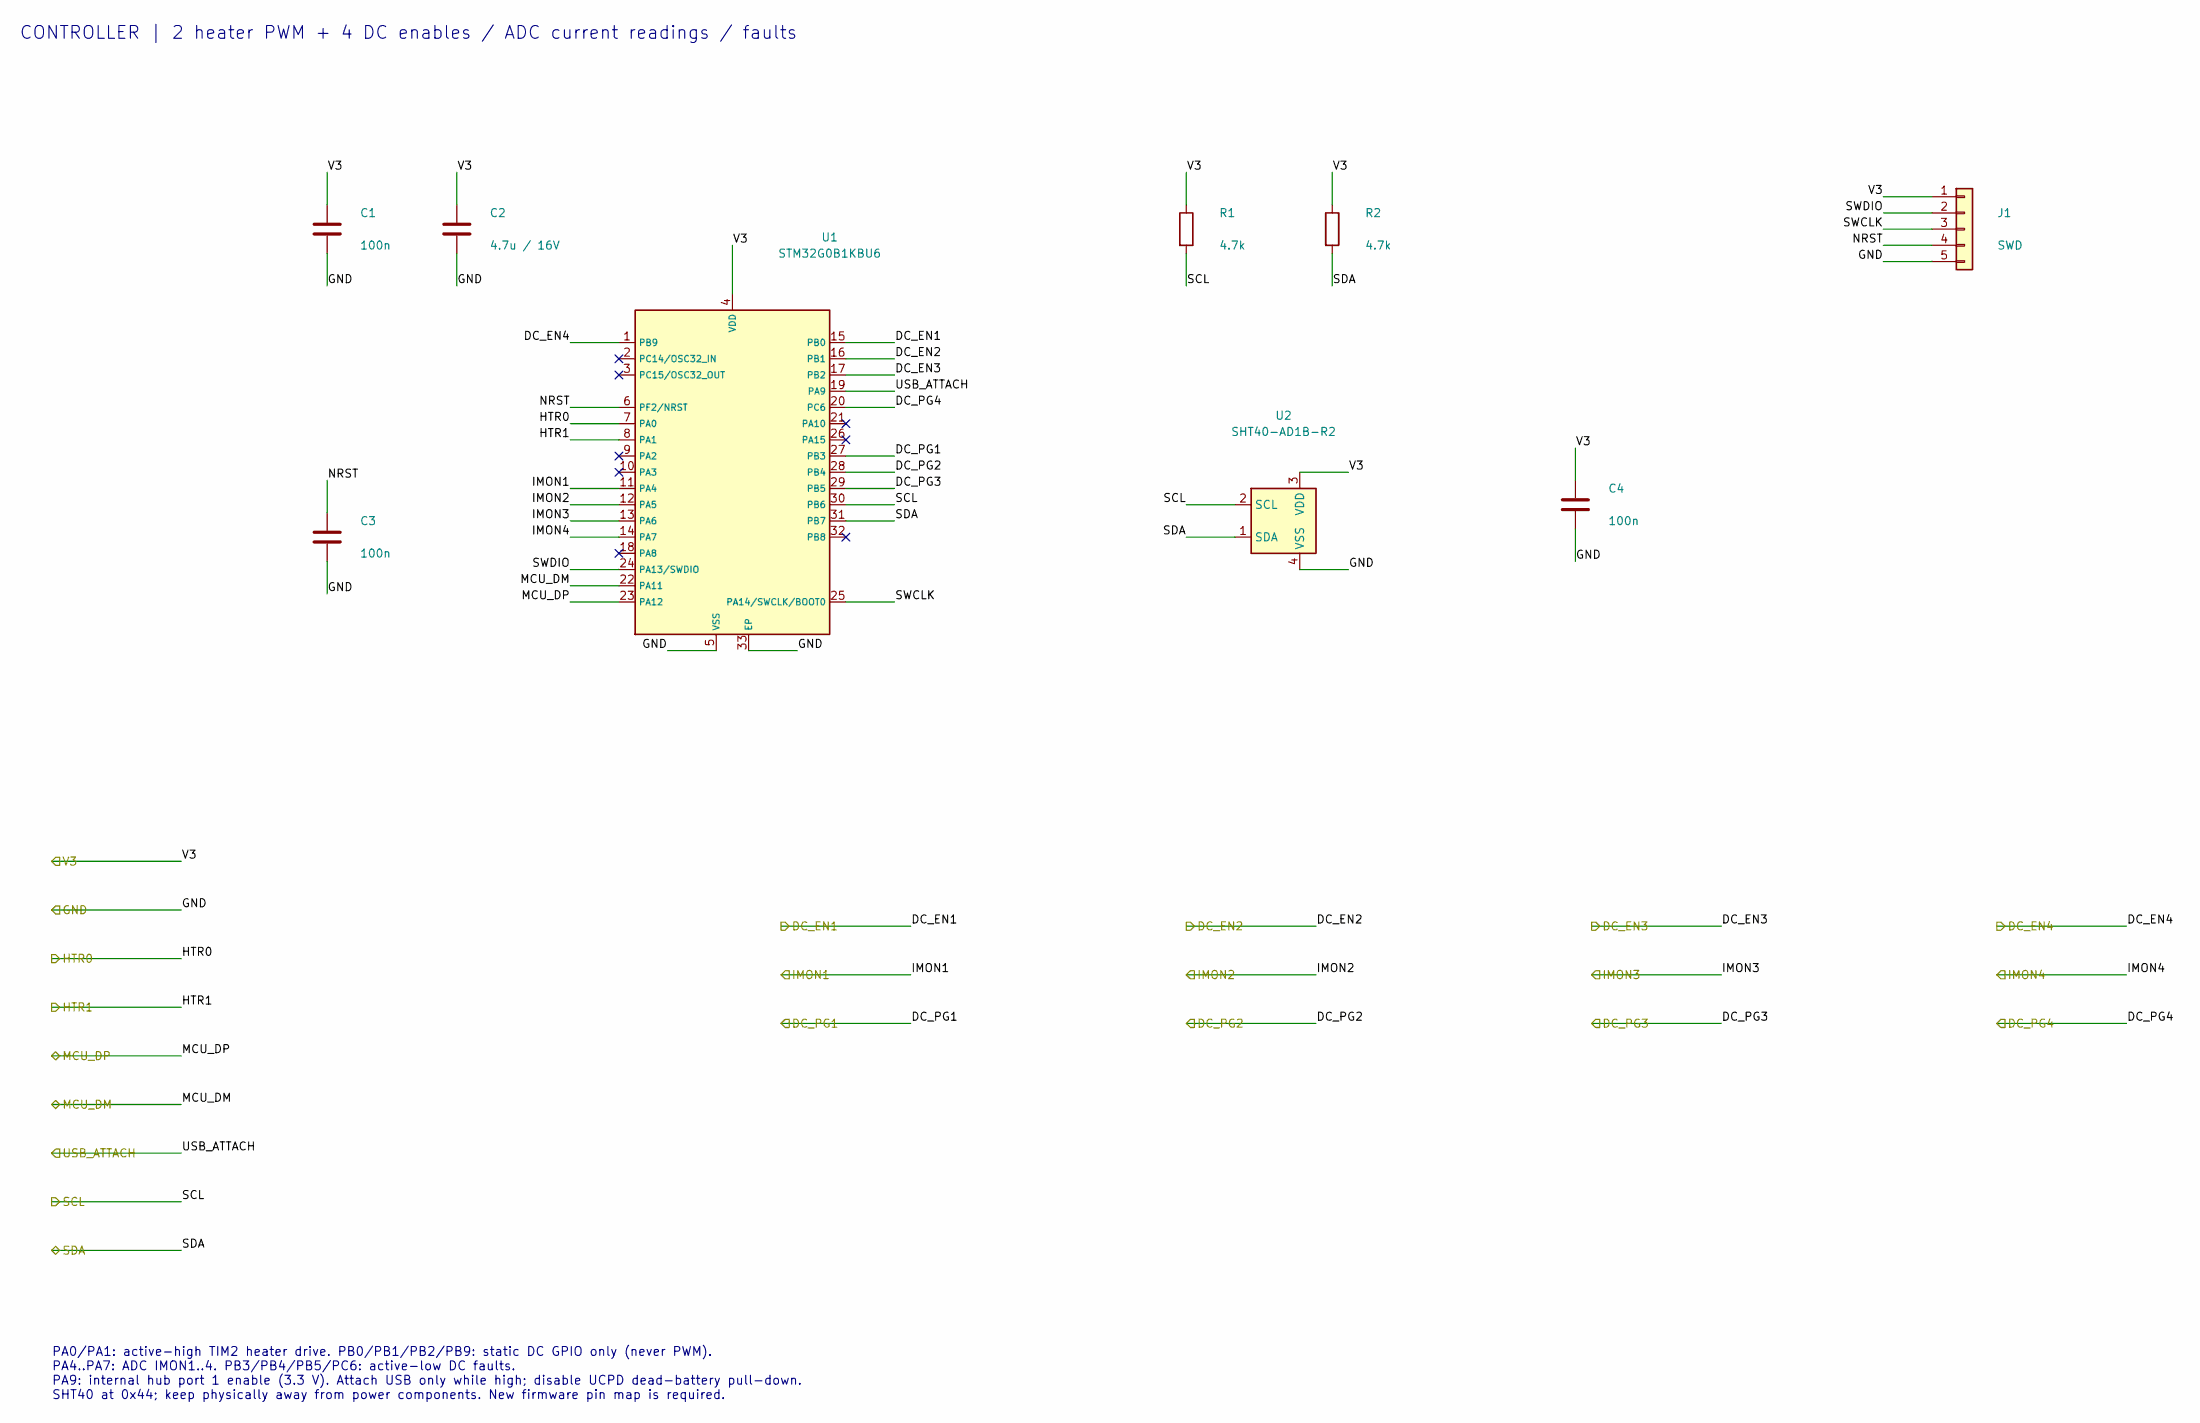
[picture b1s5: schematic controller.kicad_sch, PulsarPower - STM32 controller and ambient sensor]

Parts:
C1, C3, C4: 100n; C_0603_1608Metric; MPN CC0603KRX7R9BB104; LCSC C14663
C2: 4.7u / 16V; C_0603_1608Metric; MPN CL10A475KO8NNNC; LCSC C19666
J1: SWD; PinHeader_1x05_P2.54mm_Vertical; MPN PZ254V-11-05P; LCSC C492404
R1, R2: 4.7k; R_0603_1608Metric; MPN 0603WAF4701T5E; LCSC C23162
U1: STM32G0B1KBU6; UFQFPN-32-1EP_5x5mm_P0.5mm_EP3.5x3.5mm; MPN STM32G0B1KBU6; LCSC C5159549
U2: SHT40-AD1B-R2; Sensirion_DFN-4_1.5x1.5mm_P0.8mm_SHT4x_NoCentralPad; MPN SHT40-AD1B-R2; LCSC C2909890

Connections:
/Controller/NRST: C3.1, J1.4, U1.6 (PF2/NRST)
/Controller/SWCLK: J1.3, U1.25 (PA14/SWCLK/BOOT0)
/Controller/SWDIO: J1.2, U1.24 (PA13/SWDIO)
/DC_EN1: U1.15 (PB0); also elsewhere on the board
/DC_EN2: U1.16 (PB1); also elsewhere on the board
/DC_EN3: U1.17 (PB2); also elsewhere on the board
/DC_EN4: U1.1 (PB9); also elsewhere on the board
/DC_PG1: U1.27 (PB3); also elsewhere on the board
/DC_PG2: U1.28 (PB4); also elsewhere on the board
/DC_PG3: U1.29 (PB5); also elsewhere on the board
/DC_PG4: U1.20 (PC6); also elsewhere on the board
/GND: C1.2, C2.2, C3.2, C4.2, J1.5, U1.5 (VSS), U1.33 (EP), U2.4 (VSS); also elsewhere on the board
/HTR0: U1.7 (PA0); also elsewhere on the board
/HTR1: U1.8 (PA1); also elsewhere on the board
/IMON1: U1.11 (PA4); also elsewhere on the board
/IMON2: U1.12 (PA5); also elsewhere on the board
/IMON3: U1.13 (PA6); also elsewhere on the board
/IMON4: U1.14 (PA7); also elsewhere on the board
/MCU_DM: U1.22 (PA11); also elsewhere on the board
/MCU_DP: U1.23 (PA12); also elsewhere on the board
/SCL: R1.2, U1.30 (PB6), U2.2 (SCL); also elsewhere on the board
/SDA: R2.2, U1.31 (PB7), U2.1 (SDA); also elsewhere on the board
/USB_ATTACH: U1.19 (PA9); also elsewhere on the board
/V3: C1.1, C2.1, C4.1, J1.1, R1.1, R2.1, U1.4 (VDD), U2.3 (VDD); also elsewhere on the board

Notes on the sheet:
CONTROLLER | 2 heater PWM + 4 DC enables / ADC current readings / faults
PA0/PA1: active-high TIM2 heater drive. PB0/PB1/PB2/PB9: static DC GPIO only (never PWM). PA4..PA7: ADC IMON1..4. PB3/PB4/PB5/PC6: active-low DC faults. PA9: internal hub port 1 enable (3.3 V). Attach USB only while high; disable UCPD dead-battery pull-down. SHT40 at 0x44; keep physically away from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
